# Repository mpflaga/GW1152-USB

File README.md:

# GW1152-USB
Daughter PCB to expose USB externally

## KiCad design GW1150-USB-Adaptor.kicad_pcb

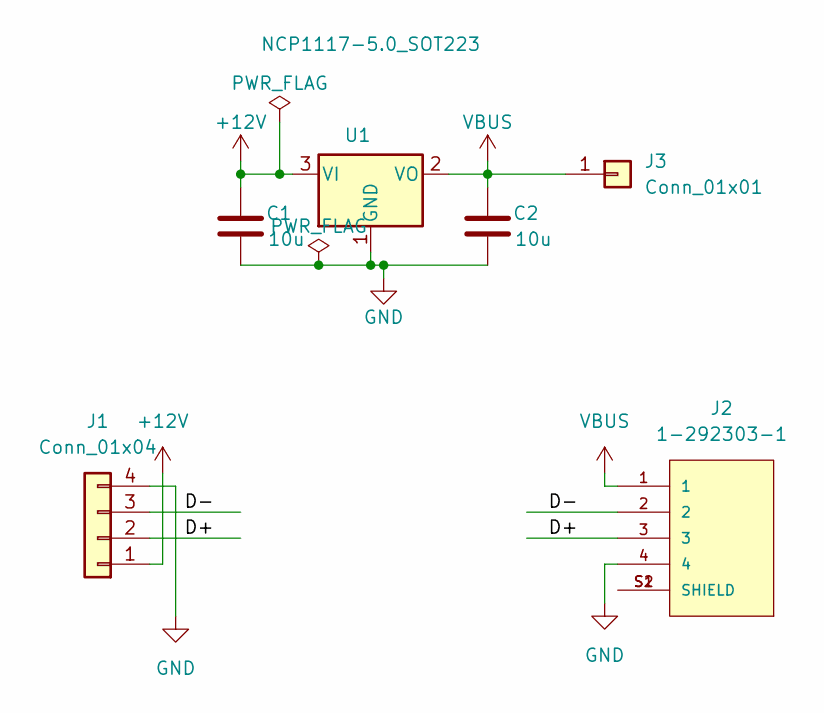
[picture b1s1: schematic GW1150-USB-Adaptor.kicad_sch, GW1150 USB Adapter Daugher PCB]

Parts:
C1, C2: 10u; C_0805_2012Metric
J1: Conn_01x04; PinHeader_1x04_P2.54mm_Horizontal
J2: 1-292303-1; TE_1-292303-1; PART_REV E12
J3: Conn_01x01; PinHeader_1x01_P2.54mm_Vertical
U1: NCP1117-5.0_SOT223; SOT-223-3_TabPin2

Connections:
+12V: C1.1, J1.1, U1.3 (VI)
/D+: J1.2, J2.3
/D-: J1.3, J2.2
GND: C1.2, C2.2, J1.4, J2.4, U1.1 (GND)
unnamed: J2.S1 (SHIELD), J2.S2 (SHIELD)
VBUS: C2.1, J2.1, J3.1, U1.2 (VO)

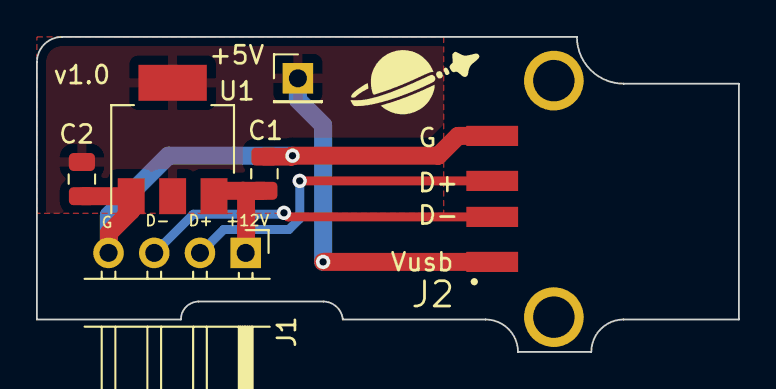
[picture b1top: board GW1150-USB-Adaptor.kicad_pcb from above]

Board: 2 copper layers, 39.0 x 17.5 mm, 6 parts (0 on the bottom side), 6 nets.

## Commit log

2023-02-08 Initial Add of files
2023-02-16 manufacturing of v0.1, initially purchased.
